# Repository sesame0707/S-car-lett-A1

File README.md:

# S(car)lett A1

## The Repository
This is the repository of the first A-line car in the [`S(car)lett`](https://github.com/sesame0707/S-car-lett) project.

## High-Level Goals
Those are the initial goals of this module:
- The use of mechanical mechanisms implemented in the LEGO 8070 set
- Design focused on easy disassembly and assembly (reusable design)
- The use of more expensive, but desirable components instead of cheaper, but weaker ones

All of the above goals have been achieved throughout this module's implementation.

## Results
The car looks as follows:

It has some custom and standard electronic parts in it. The real photos of them can be accessed in the `Pictures/Real photos` folder. For the standard parts, refer to the table of parts that can be found in the `Documentation/General` folder. Moreover, this model also incorporates 3D-printed parts, which can be accessed in the `3D printed parts` folder.

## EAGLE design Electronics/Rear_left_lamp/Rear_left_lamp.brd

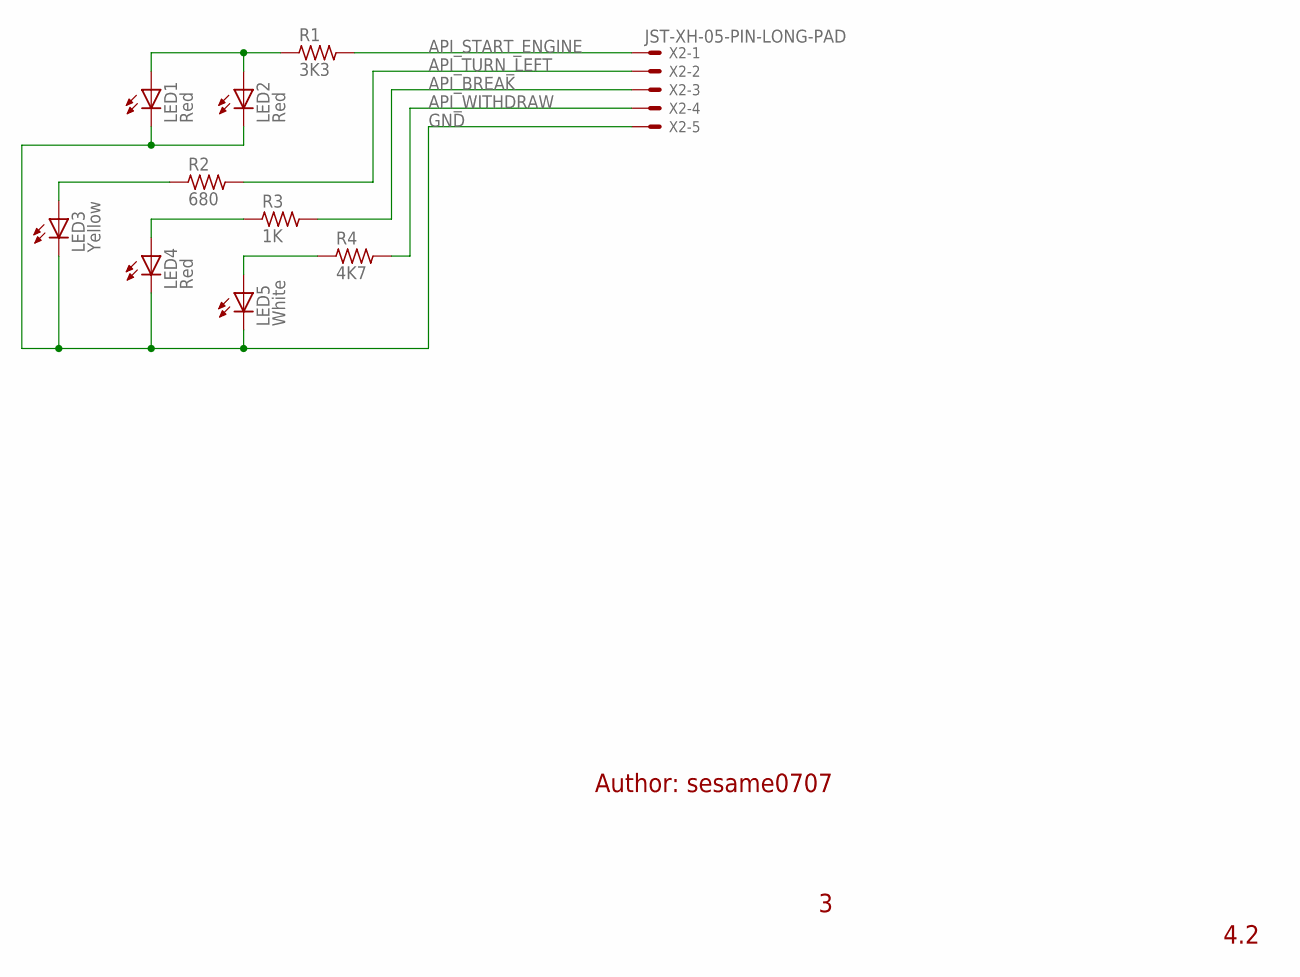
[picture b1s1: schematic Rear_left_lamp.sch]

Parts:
LED1, LED2, LED4: Red; LED5MM; VOLTAGE_EMPIRICAL 1.83 V; MANUFACTURER_PART_NUMBER LL-503VD2E-1B
LED3: Yellow; LED5MM; VOLTAGE_EMPIRICAL 1.88 V; MANUFACTURER_PART_NUMBER LL-503YD2E-1B
LED5: White; LED5MM; VOLTAGE_EMPIRICAL 2.58 V; MANUFACTURER_PART_NUMBER LL-504WC2V-W2-3PD
R1: 3K3; R1206; MANUFACTURER_PART_NUMBER 1206S4J0332T5E
R2: 680; R1206; MANUFACTURER_PART_NUMBER 1206S4J0681T5E
R3: 1K; R1206; MANUFACTURER_PART_NUMBER 1206S4J0102T5E
R4: 4K7; R1206; MANUFACTURER_PART_NUMBER 1206S4J0472T5E
X2: JST-XH-05-PIN-LONG-PAD; JST-XH-05-PACKAGE-LONG-PAD

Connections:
API_BREAK: R3.2, X2.3
API_START_ENGINE: LED1.A, LED2.A, R1.1
API_TURN_LEFT: R2.2, X2.2
API_WITHDRAW: R4.2, X2.4
GND: LED1.K (C), LED2.K (C), LED3.K (C), LED4.K (C), LED5.K (C), X2.5
unnamed: LED3.A, R2.1
unnamed: R1.2, X2.1
unnamed: LED4.A, R3.1
unnamed: LED5.A, R4.1

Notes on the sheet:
Author: sesame0707
4.2

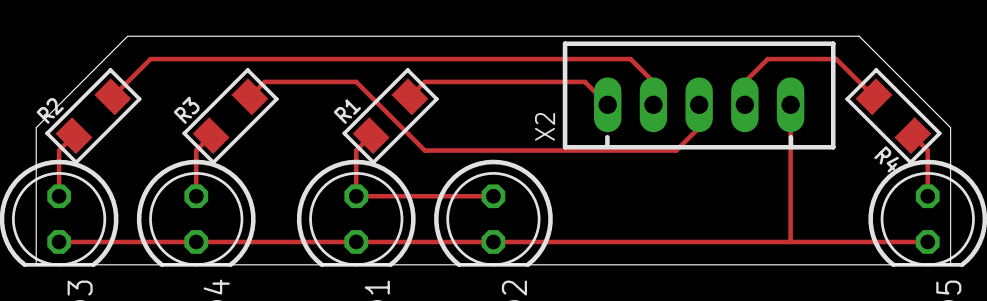
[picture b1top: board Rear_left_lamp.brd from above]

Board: 2 copper layers, 50.8 x 12.7 mm, 10 parts (0 on the bottom side), 9 nets.

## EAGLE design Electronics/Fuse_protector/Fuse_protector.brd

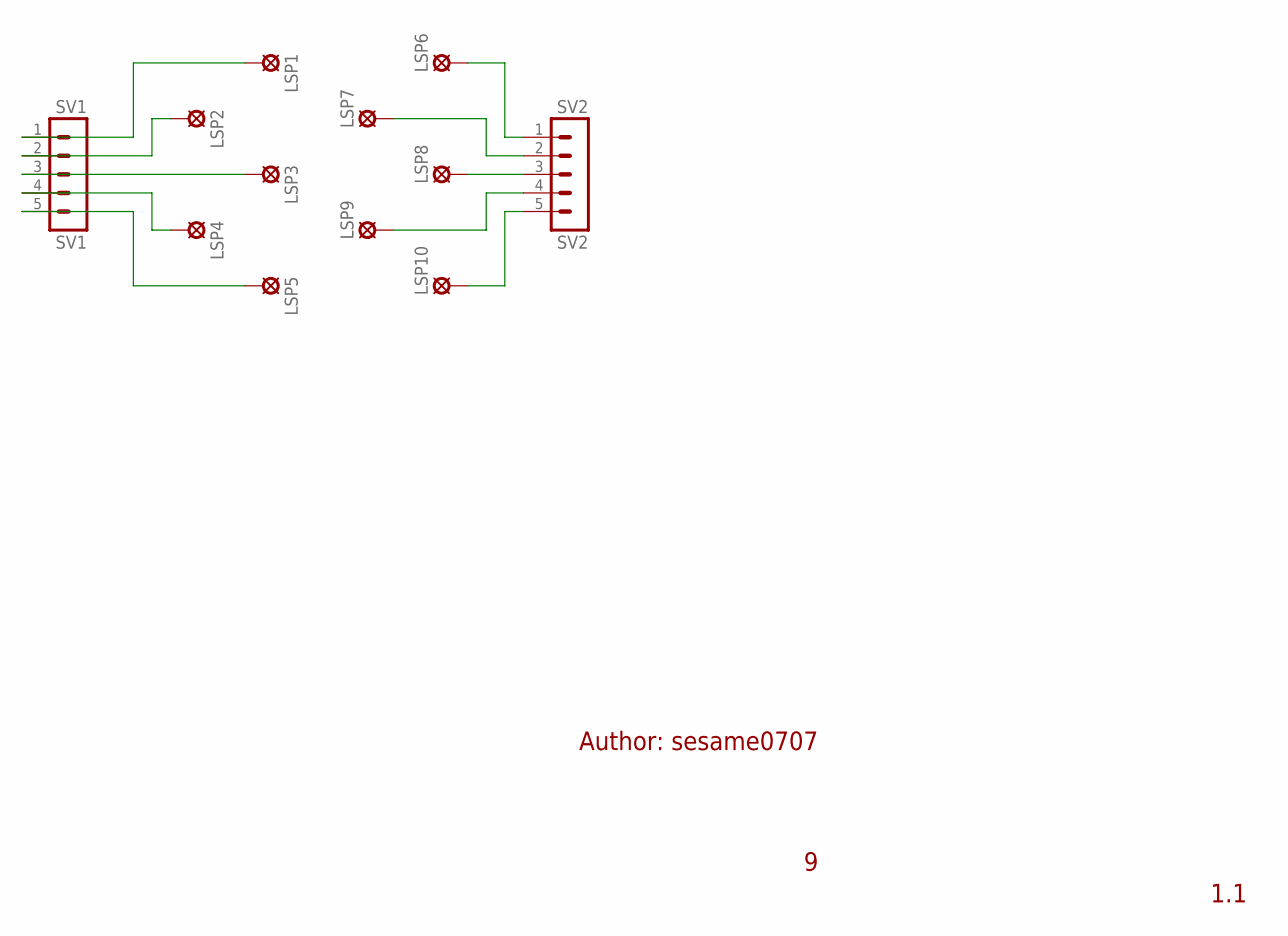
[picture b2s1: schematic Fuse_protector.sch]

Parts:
LSP1, LSP2, LSP3, LSP4, LSP5, LSP6, LSP7, LSP8, LSP9, LSP10: SE14
SV1: SV1; MA05-1
SV2: SV2; MA05-1

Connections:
unnamed: LSP1.MP, SV1.1
unnamed: LSP2.MP, SV1.2
unnamed: LSP3.MP, SV1.3
unnamed: LSP4.MP, SV1.4
unnamed: LSP5.MP, SV1.5
unnamed: LSP6.MP, SV2.1
unnamed: LSP7.MP, SV2.2
unnamed: LSP8.MP, SV2.3
unnamed: LSP9.MP, SV2.4
unnamed: LSP10.MP, SV2.5

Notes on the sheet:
Author: sesame0707
1.1

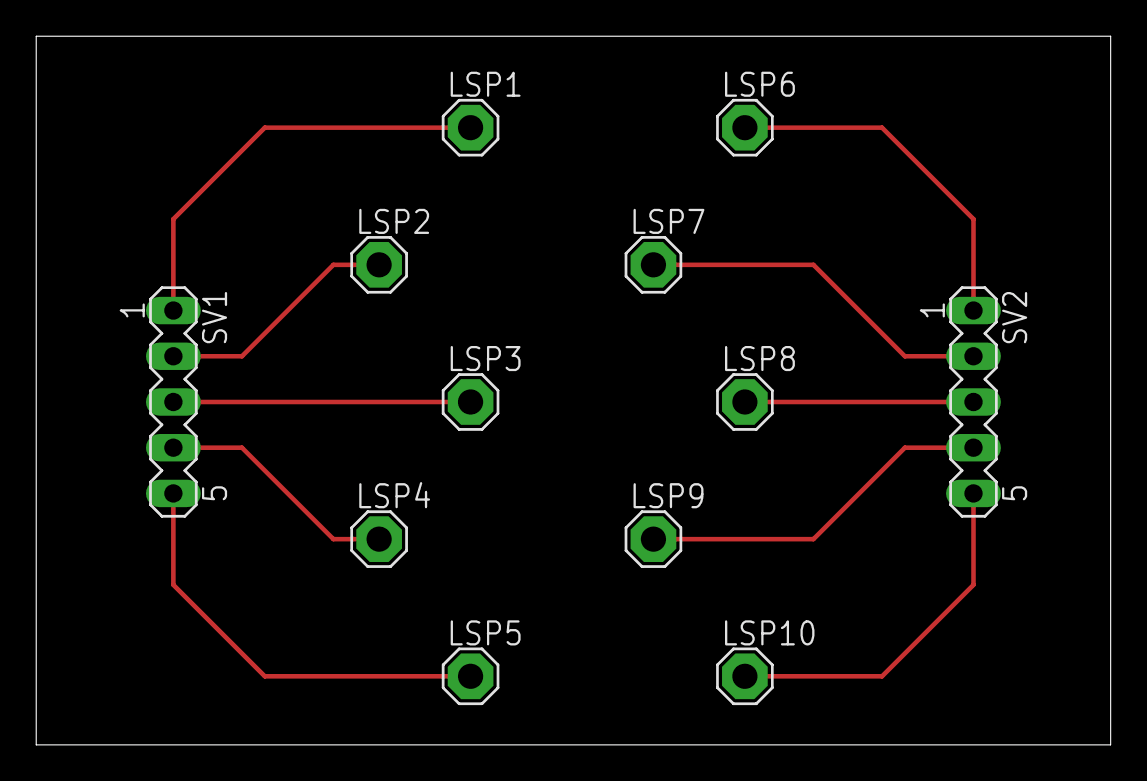
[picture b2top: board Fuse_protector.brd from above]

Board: 2 copper layers, 59.7 x 39.4 mm, 12 parts (0 on the bottom side), 10 nets.

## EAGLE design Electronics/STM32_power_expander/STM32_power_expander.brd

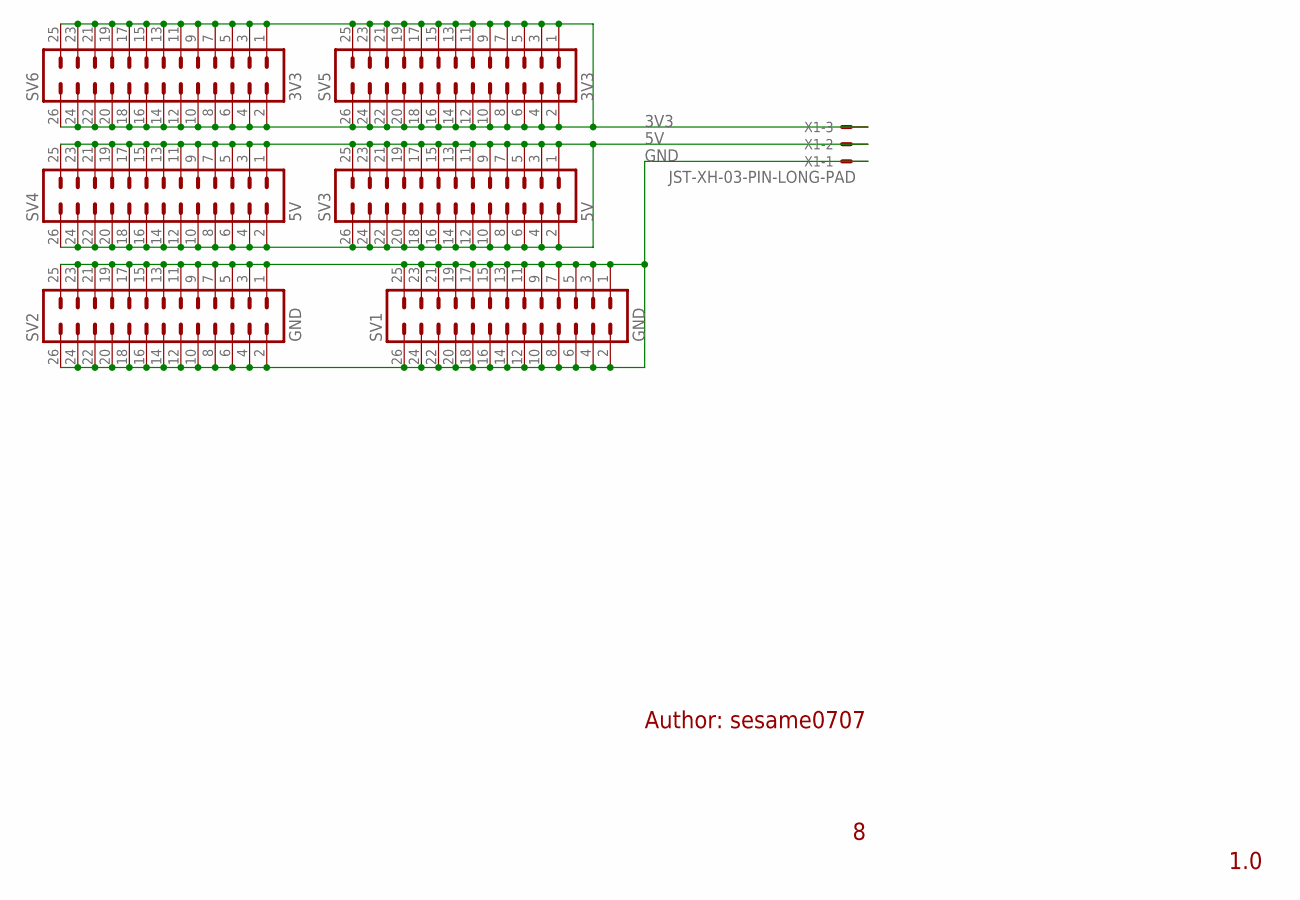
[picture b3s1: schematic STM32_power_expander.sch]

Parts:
SV1, SV2: GND; MA13-2
SV3, SV4: 5V; MA13-2
SV5, SV6: 3V3; MA13-2
X1: JST-XH-03-PIN-LONG-PAD; JST-XH-03-PACKAGE-LONG-PAD

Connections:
3V3: SV5.1, SV5.2, SV5.3, SV5.4, SV5.5, SV5.6, SV5.7, SV5.8, SV5.9, SV5.10, SV5.11, SV5.12, SV5.13, SV5.14, SV5.15, SV5.16, SV5.17, SV5.18, SV5.19, SV5.20, SV5.21, SV5.22, SV5.23, SV5.24, SV5.25, SV5.26, SV6.1, SV6.2, SV6.3, SV6.4, SV6.5, SV6.6, SV6.7, SV6.8, SV6.9, SV6.10, SV6.11, SV6.12, SV6.13, SV6.14, SV6.15, SV6.16, SV6.17, SV6.18, SV6.19, SV6.20, SV6.21, SV6.22, SV6.23, SV6.24, SV6.25, SV6.26, X1.3
5V: SV3.1, SV3.2, SV3.3, SV3.4, SV3.5, SV3.6, SV3.7, SV3.8, SV3.9, SV3.10, SV3.11, SV3.12, SV3.13, SV3.14, SV3.15, SV3.16, SV3.17, SV3.18, SV3.19, SV3.20, SV3.21, SV3.22, SV3.23, SV3.24, SV3.25, SV3.26, SV4.1, SV4.2, SV4.3, SV4.4, SV4.5, SV4.6, SV4.7, SV4.8, SV4.9, SV4.10, SV4.11, SV4.12, SV4.13, SV4.14, SV4.15, SV4.16, SV4.17, SV4.18, SV4.19, SV4.20, SV4.21, SV4.22, SV4.23, SV4.24, SV4.25, SV4.26, X1.2
GND: SV1.1, SV1.2, SV1.3, SV1.4, SV1.5, SV1.6, SV1.7, SV1.8, SV1.9, SV1.10, SV1.11, SV1.12, SV1.13, SV1.14, SV1.15, SV1.16, SV1.17, SV1.18, SV1.19, SV1.20, SV1.21, SV1.22, SV1.23, SV1.24, SV1.25, SV1.26, SV2.1, SV2.2, SV2.3, SV2.4, SV2.5, SV2.6, SV2.7, SV2.8, SV2.9, SV2.10, SV2.11, SV2.12, SV2.13, SV2.14, SV2.15, SV2.16, SV2.17, SV2.18, SV2.19, SV2.20, SV2.21, SV2.22, SV2.23, SV2.24, SV2.25, SV2.26, X1.1

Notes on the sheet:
Author: sesame0707
1.0

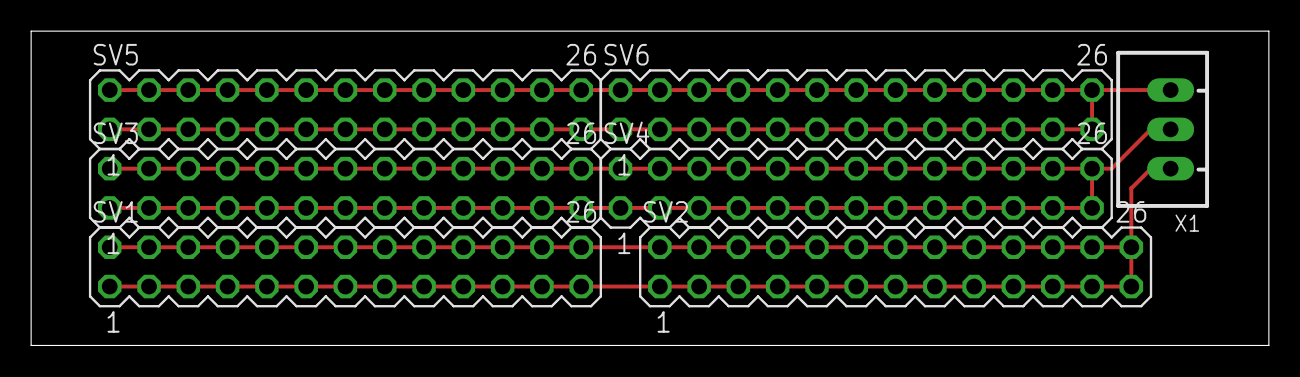
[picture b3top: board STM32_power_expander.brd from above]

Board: 2 copper layers, 80.0 x 20.3 mm, 7 parts (0 on the bottom side), 3 nets.

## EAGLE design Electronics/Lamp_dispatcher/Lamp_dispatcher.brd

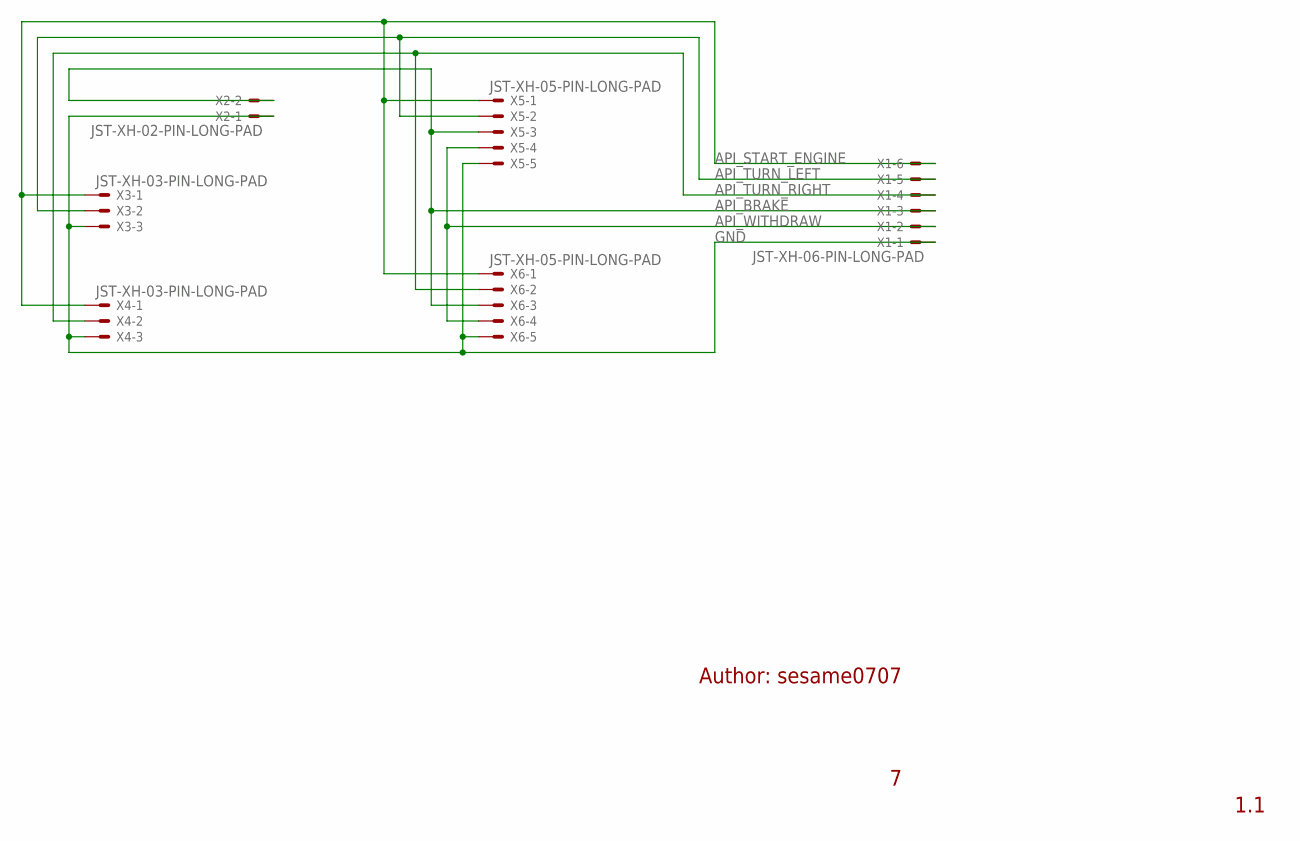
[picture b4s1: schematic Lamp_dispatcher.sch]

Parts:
X1: JST-XH-06-PIN-LONG-PAD; JST-XH-06-PACKAGE-LONG-PAD
X2: JST-XH-02-PIN-LONG-PAD; JST-XH-02-PACKAGE-LONG-PAD
X3, X4: JST-XH-03-PIN-LONG-PAD; JST-XH-03-PACKAGE-LONG-PAD
X5, X6: JST-XH-05-PIN-LONG-PAD; JST-XH-05-PACKAGE-LONG-PAD

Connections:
API_BRAKE: X1.3, X2.2, X5.3, X6.3
API_START_ENGINE: X1.6, X3.1, X4.1, X5.1, X6.1
API_TURN_LEFT: X1.5, X3.2, X5.2
API_TURN_RIGHT: X1.4, X4.2, X6.2
API_WITHDRAW: X1.2, X5.4, X6.4
GND: X1.1, X2.1, X3.3, X4.3, X5.5, X6.5

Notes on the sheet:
Author: sesame0707
1.1

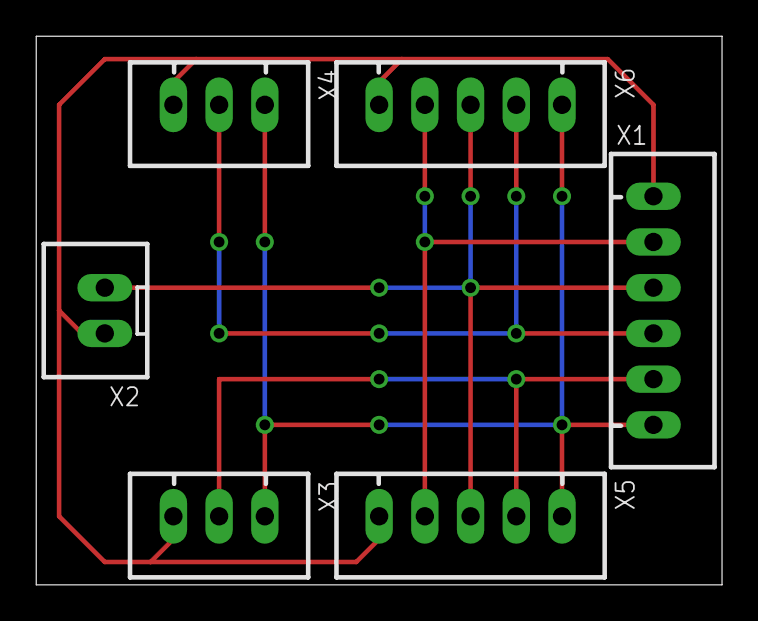
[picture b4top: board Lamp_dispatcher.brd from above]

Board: 2 copper layers, 38.1 x 30.5 mm, 6 parts (0 on the bottom side), 6 nets.

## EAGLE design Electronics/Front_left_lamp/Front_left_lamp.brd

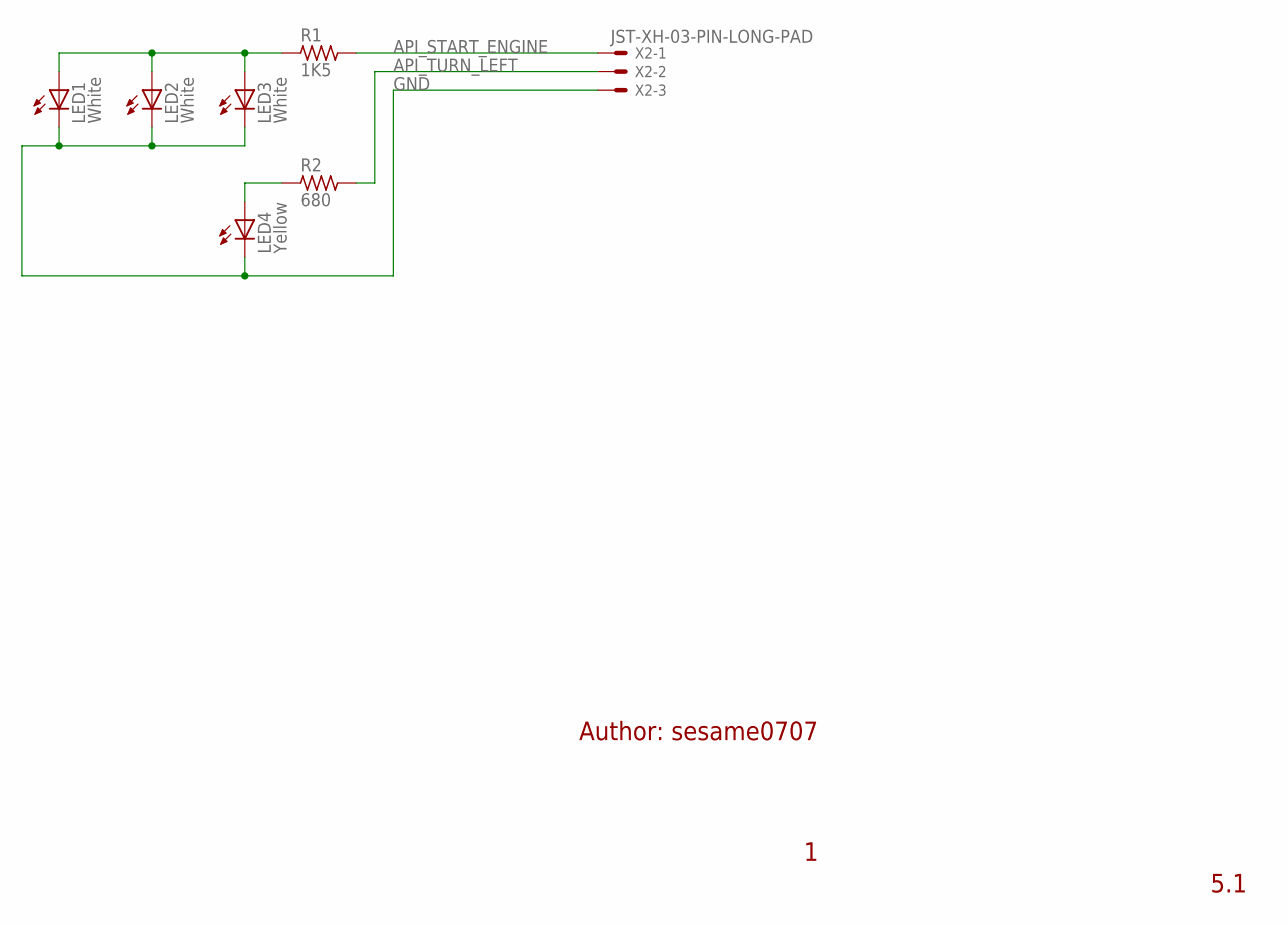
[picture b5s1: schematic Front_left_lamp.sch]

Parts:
LED1, LED2, LED3: White; LED5MM; VOLTAGE_EMPIRICAL 2.58 V; MANUFACTURER_PART_NUMBER LL-504WC2V-W2-3PD
LED4: Yellow; LED5MM; VOLTAGE_EMPIRICAL 1.88 V; MANUFACTURER_PART_NUMBER LL-503YD2E-1B
R1: 1K5; R1206; MANUFACTURER_PART_NUMBER 1206S4J0152T5E
R2: 680; R1206; MANUFACTURER_PART_NUMBER 1206S4J0681T5E
X2: JST-XH-03-PIN-LONG-PAD; JST-XH-03-PACKAGE-LONG-PAD

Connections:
API_START_ENGINE: LED1.A, LED2.A, LED3.A, R1.1
API_TURN_LEFT: R2.2, X2.2
GND: LED1.K (C), LED2.K (C), LED3.K (C), LED4.K (C), X2.3
unnamed: R1.2, X2.1
unnamed: LED4.A, R2.1

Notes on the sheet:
Author: sesame0707
5.1

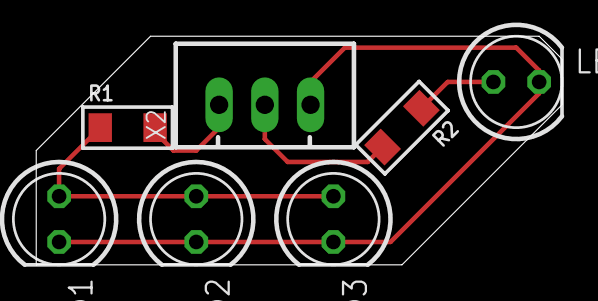
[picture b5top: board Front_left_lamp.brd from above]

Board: 2 copper layers, 29.2 x 12.7 mm, 7 parts (0 on the bottom side), 5 nets.

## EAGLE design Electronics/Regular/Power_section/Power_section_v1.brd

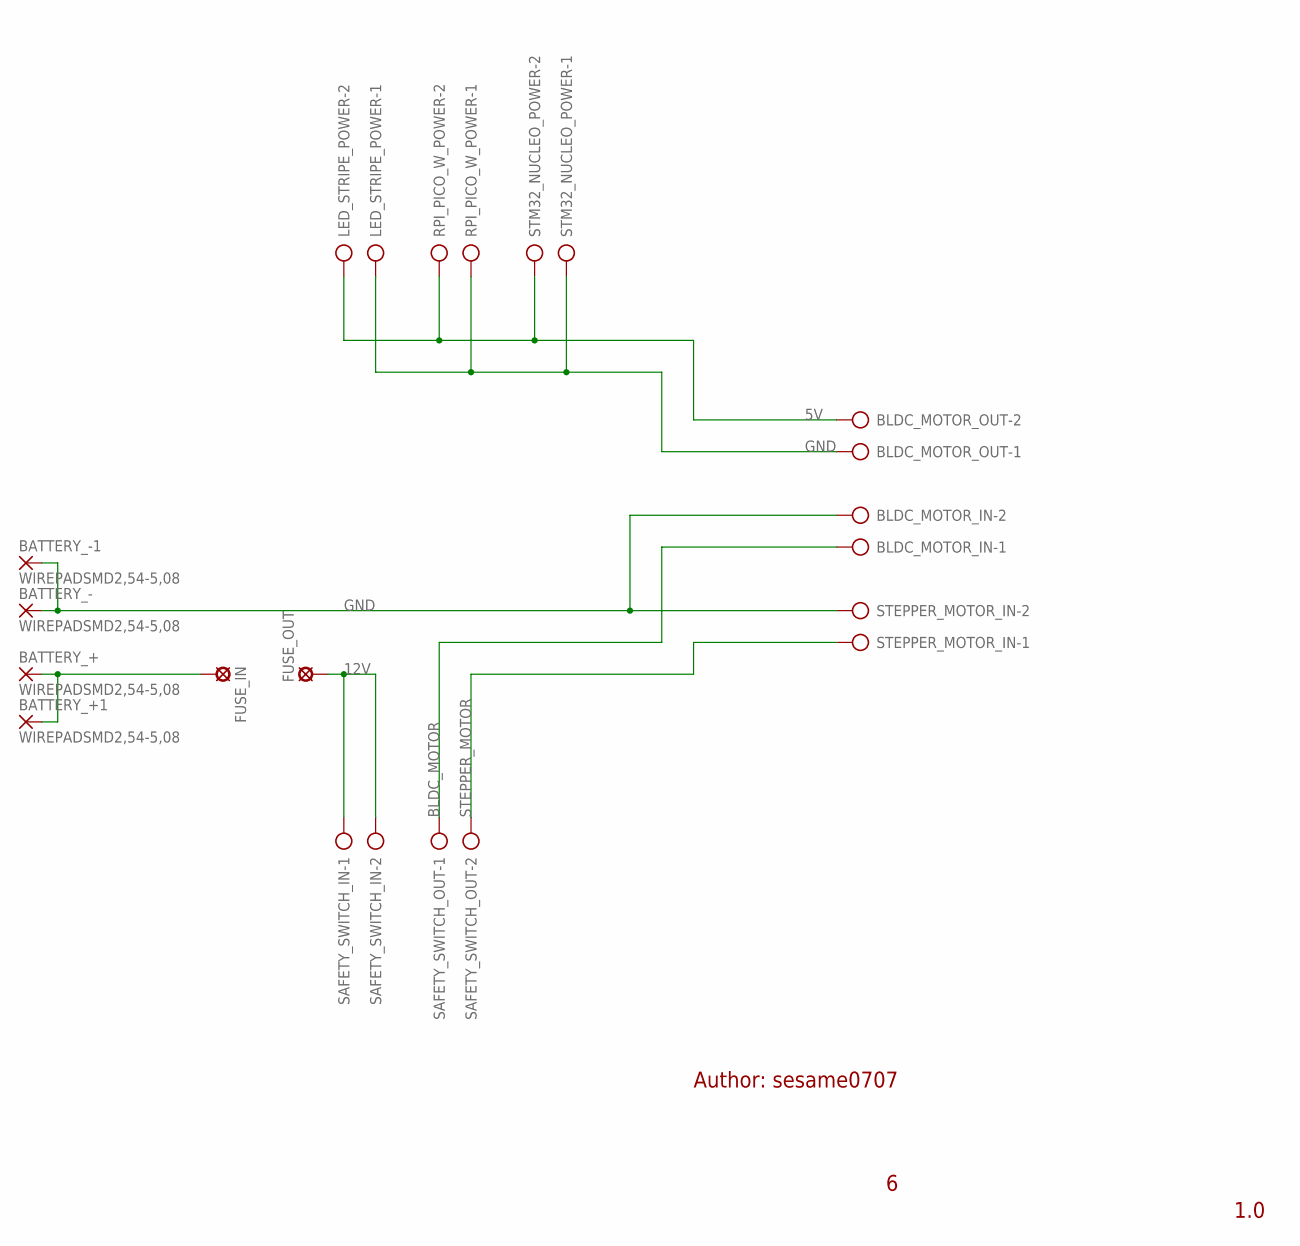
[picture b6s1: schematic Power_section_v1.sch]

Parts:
BATTERY_+, BATTERY_+1: WIREPADSMD2,54-5,08; SMD2,54-5,08
BATTERY_-, BATTERY_-1: WIREPADSMD2,54-5,08; SMD2,54-5,08
BLDC_MOTOR_IN: AK500/2
BLDC_MOTOR_OUT: AK500/2
FUSE_IN: SE14
FUSE_OUT: SE14
LED_STRIPE_POWER: AK500/2
RPI_PICO_W_POWER: AK500/2
SAFETY_SWITCH_IN: AK500/2
SAFETY_SWITCH_OUT: AK500/2
STEPPER_MOTOR_IN: AK500/2
STM32_NUCLEO_POWER: AK500/2

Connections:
5V: BLDC_MOTOR_OUT.2, LED_STRIPE_POWER.2, RPI_PICO_W_POWER.2, STM32_NUCLEO_POWER.2
12V: FUSE_OUT.MP, SAFETY_SWITCH_IN.1, SAFETY_SWITCH_IN.2
BLDC_MOTOR: BLDC_MOTOR_IN.1, SAFETY_SWITCH_OUT.1
GND: BATTERY_-.1, BATTERY_-1.1, BLDC_MOTOR_IN.2, BLDC_MOTOR_OUT.1, LED_STRIPE_POWER.1, RPI_PICO_W_POWER.1, STEPPER_MOTOR_IN.2, STM32_NUCLEO_POWER.1
unnamed: BATTERY_+.1, BATTERY_+1.1, FUSE_IN.MP
STEPPER_MOTOR: SAFETY_SWITCH_OUT.2, STEPPER_MOTOR_IN.1

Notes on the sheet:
Author: sesame0707
1.0

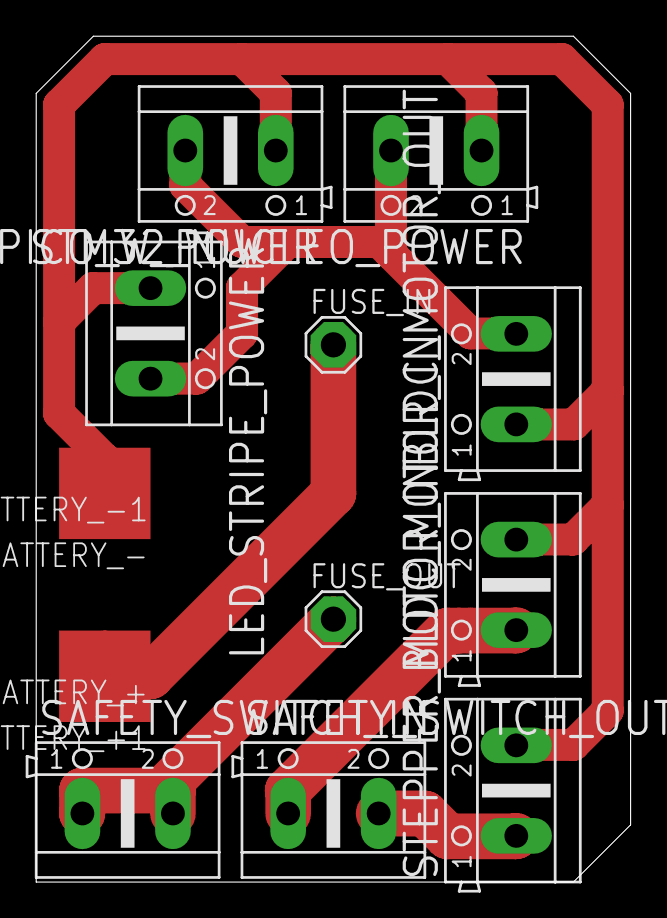
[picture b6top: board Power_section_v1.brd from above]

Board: 2 copper layers, 33.0 x 47.0 mm, 14 parts (0 on the bottom side), 6 nets.

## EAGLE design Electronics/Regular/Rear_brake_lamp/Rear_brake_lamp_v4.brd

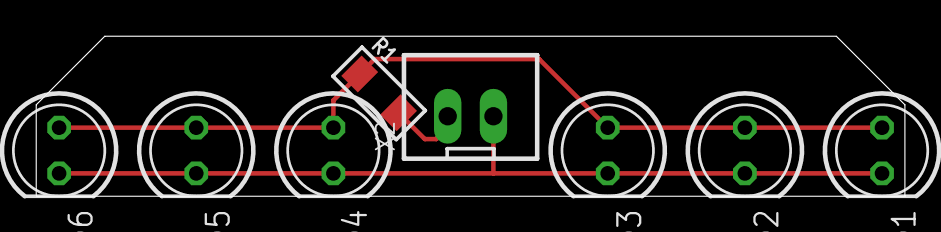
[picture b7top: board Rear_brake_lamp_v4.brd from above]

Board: 2 copper layers, 48.3 x 8.9 mm, 8 parts (0 on the bottom side), 3 nets.

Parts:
LED1, LED2, LED3, LED4, LED5, LED6: 1.78 V; LED5MM
R1: 120; R1206
X2: JST-XH-02-PIN-LONG-PAD; JST-XH-02-PACKAGE-LONG-PAD

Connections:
API_BRAKE: LED1.A, LED2.A, LED3.A, LED4.A, LED5.A, LED6.A, R1.1
GND: LED1.K, LED2.K, LED3.K, LED4.K, LED5.K, LED6.K, X2.2
unnamed: R1.2, X2.1

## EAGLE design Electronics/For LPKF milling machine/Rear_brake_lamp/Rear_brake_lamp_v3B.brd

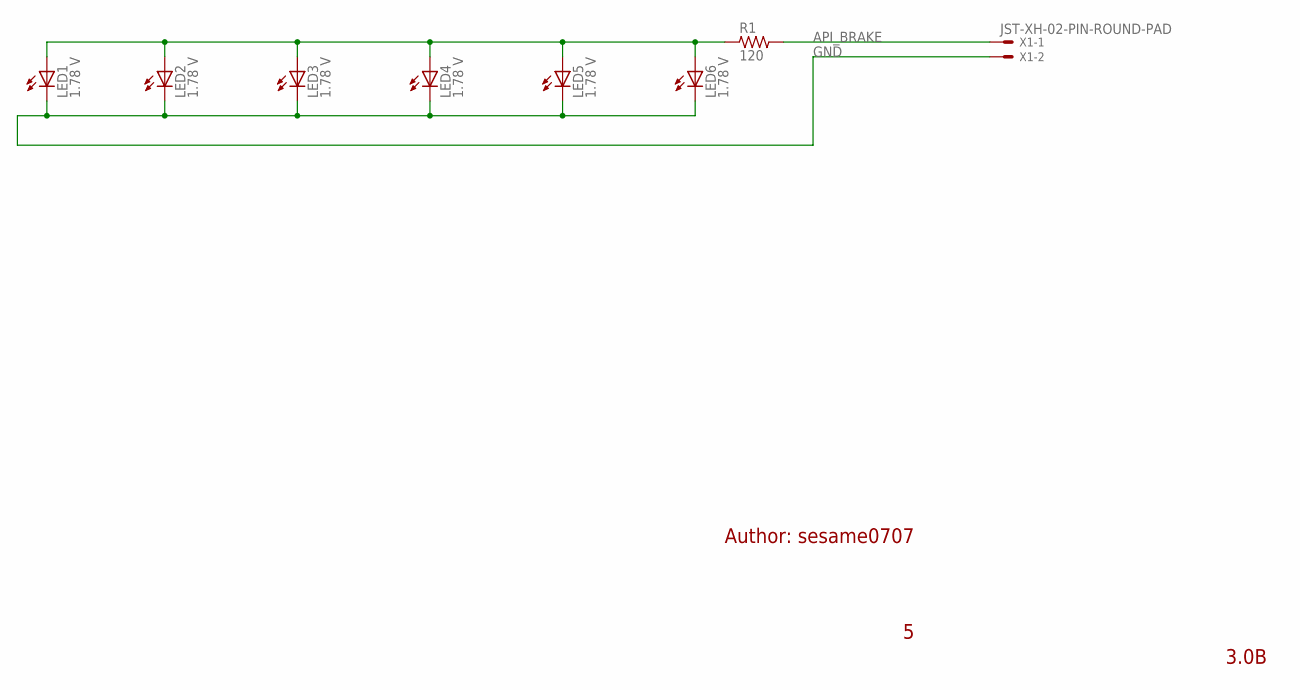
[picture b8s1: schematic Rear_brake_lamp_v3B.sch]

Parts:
LED1, LED2, LED3, LED4, LED5, LED6: 1.78 V; LED5MM
R1: 120; R1206
X1: JST-XH-02-PIN-ROUND-PAD; JST-XH-02-PACKAGE-ROUND-PAD

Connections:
API_BRAKE: LED1.A, LED2.A, LED3.A, LED4.A, LED5.A, LED6.A, R1.1
GND: LED1.K (C), LED2.K (C), LED3.K (C), LED4.K (C), LED5.K (C), LED6.K (C), X1.2
unnamed: R1.2, X1.1

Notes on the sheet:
Author: sesame0707
3.0B

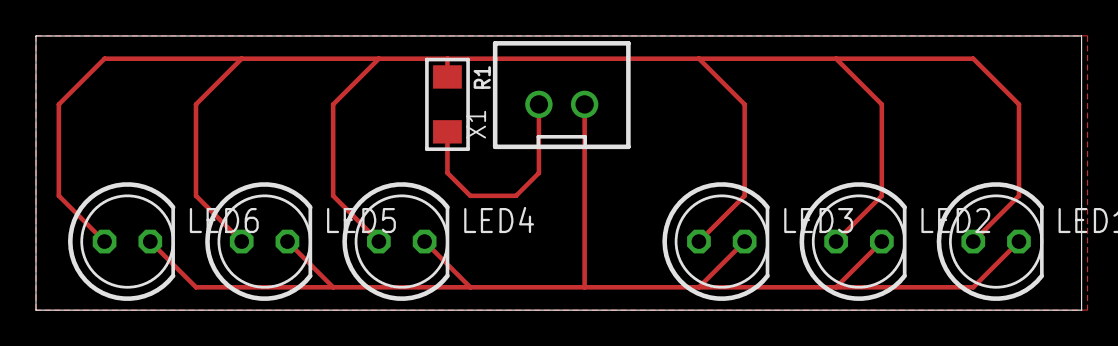
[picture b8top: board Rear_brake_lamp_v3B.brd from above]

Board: 2 copper layers, 58.1 x 15.2 mm, 8 parts (0 on the bottom side), 3 nets.

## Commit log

2023-08-17 Added list of parts and official LEGO manuals
2023-08-23 List of parts updated
2023-08-29 LED stripe tested
2023-10-11 Electronics folder created
2023-10-11 LEDs test project done
2023-10-13 Front_left_lamp done
2023-10-23 Front lamps done
2023-10-23 Front and rear lamps done
2023-10-27 Rear brake lamp started
2023-10-29 Rear brake lamp done
2023-10-31 Rear lamps improved
    Greater resistors' value for API_START_ENGINE
2023-11-02 LICENSE.md file created
2023-11-12 All lamps improved
    Refactoring into only "top" layer done
2023-11-18 All lamps improved
    Refactoring into less, but more powerful resistors done
2023-11-18 Tests folder removed
2023-11-23 Split into "Regular" and "For LPKF milling machine" branches done
2023-12-07 Power section done
2023-12-07 All lamps improved
    Refactoring includes:
    - dimension minimalization,
    - removal of the common ground plane,
    - anti-short circuit placement of components,
    - replacement of round pads with the long ones
2023-12-08 Power section improved
    What has been improved:
    - changed fuse holder slot for the smaller model,
    - made wires wider
2023-12-08 Power section improved
    What has been improved:
    - moved BAT+ and BAT- pads to the very left,
    - made wires wider
2023-12-11 Export for milling done
2023-12-19 BOM on front lamps added
2023-12-20 BOM on all the lamps added
    Note: Version of lamps' projects has increased from x.0 to x.1.
    What also has been done:
    - some visual refactoring on schematics
2023-12-20 Transition to revision-only versioning system done
2024-01-25 Lamp dispatcher done
2024-02-01 Lamp dispatcher improved
    What has been improved:
    - rotated 2- and 6-pin JST connectors,
    - corrected PCB dimensions,
    - curved GND wire
2024-02-01 Fuse protector done
2024-02-01 STM32 power expander done
2024-02-01 Backup files removed
2024-02-01 Components' power draw updated
2024-02-01 Fuse protector improved
    What has been improved:
    - corrected size of space for fuses
2024-02-03 Rear lamps improved
    What has been improved:
    - changed API_START_ENGINE red LEDs' CURRENT_EMPIRICAL value one decimal point smaller
2024-02-15 Battery information file added
2024-02-16 Battery percentage order reversed
2024-02-19 Electronic modules documentation' folder added
    Electronic modules documentation' pattern is "[main_module] functionality - manufacturer". Re-download of all the documentation also has been done due to up-to-date insurance
2024-02-19 Files' rearrangement done
2024-02-19 Li-Po battery voltage characteristics added
2024-02-20 .gitignore file implemented
2024-02-22 List of parts updated
    Refactoring also has been done
2024-02-23 Components' power draw updated
    Measured RPi's power draw under load
2024-03-06 Components' power draw updated
    Measured battery charge level indicators' power draw and updated total power draw
2024-03-06 Battery charged
2024-04-08 LEGO standard worked out
2024-04-08 Part "1. Stepper motor holder (L)" done
2024-04-10 Part "2. Stepper motor holder (R)" done
2024-04-11 Part "3. BLDC motor holder" done
2024-04-11 Part "4. BLDC motor transmission 7x bar" done
2024-04-12 Part "3. BLDC motor holder" improved
2024-04-19 File arrangement done
2024-04-19 Logos moved
2024-08-19 Update the .gitignore file
2024-08-29 Update README.md
    Also added new pictures

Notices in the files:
parts and their libraries:
rc-master-smd: Copyright (C) 2007, Bob Starr
